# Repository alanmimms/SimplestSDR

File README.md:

# SimplestSDR
Very simple SDR to build on a breadboard to demonstrate SDR principles driving a PC sound input for I/Q.

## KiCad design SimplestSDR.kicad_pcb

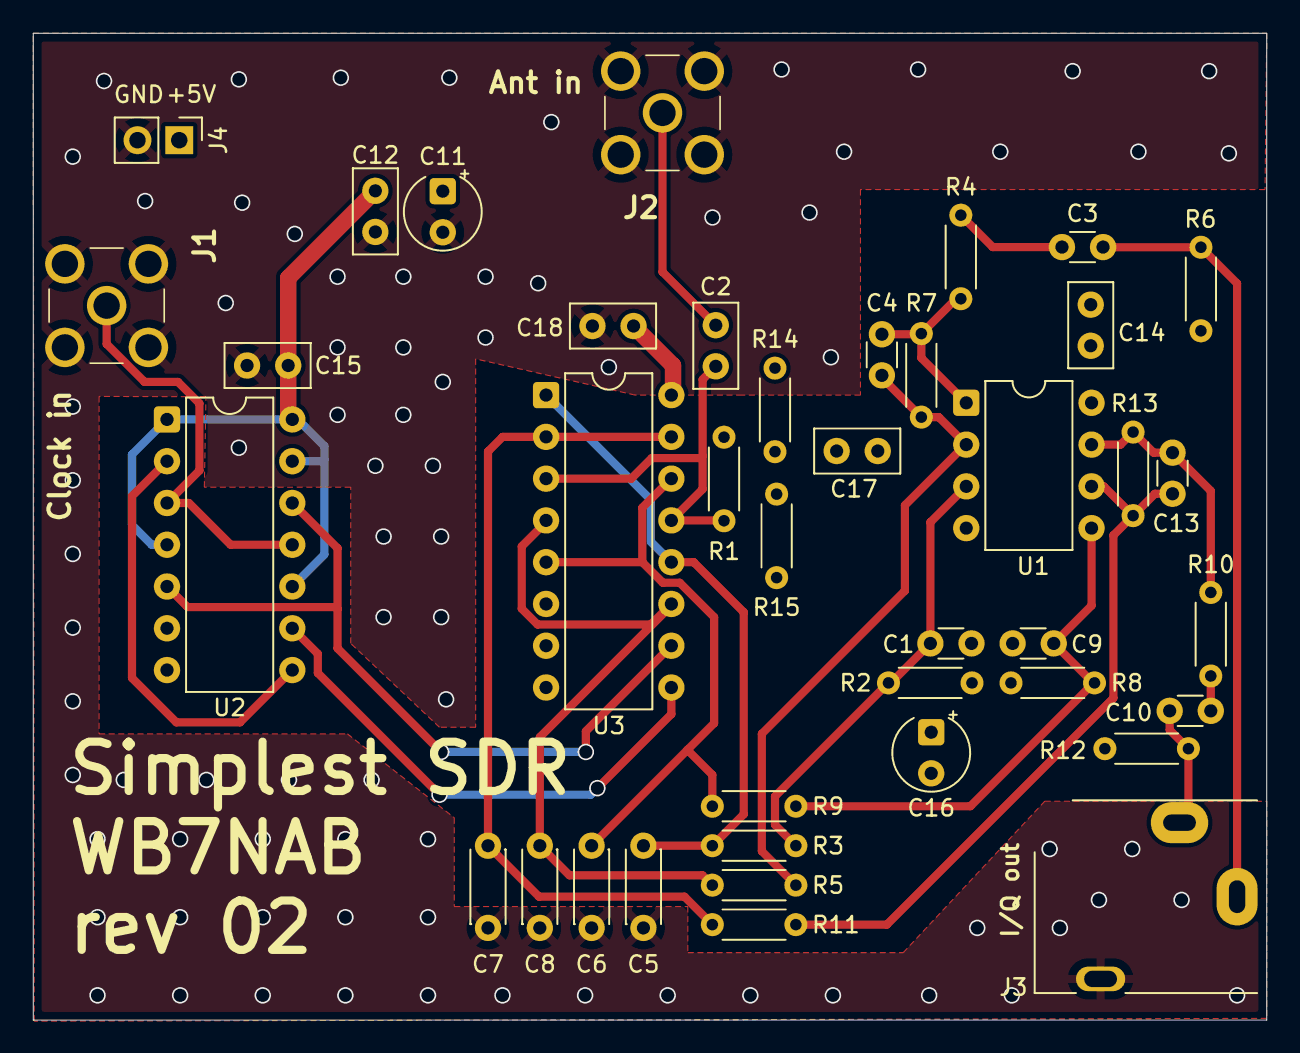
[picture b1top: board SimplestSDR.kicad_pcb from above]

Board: 2 copper layers, 75.0 x 60.0 mm, 40 parts (0 on the bottom side), 23 nets.

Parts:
C1, C4, C9, C13: 100pF; C_Disc_D3.0mm_W1.6mm_P2.50mm
C2, C12, C14, C15, C17, C18: 100nF; C_Disc_D5.0mm_W2.5mm_P2.50mm
C3, C10: 1uF; C_Disc_D3.0mm_W1.6mm_P2.50mm
C5, C6, C7, C8: 4.7nF; C_Disc_D4.3mm_W1.9mm_P5.00mm
C11, C16: 10uF; CP_Radial_Tantal_D4.5mm_P2.50mm
J1: Clock in; SMAJPHRATH1
J2: Ant in; SMAJPHRATH1
J3: I/Q out; Jack_3.5mm_CUI_SJ1-3513N_Horizontal
J4: +5V; PinHeader_1x02_P2.54mm_Vertical
R1: 1k; R_Axial_DIN0204_L3.6mm_D1.6mm_P5.08mm_Horizontal
R2, R6, R7, R8, R12, R13: 100k; R_Axial_DIN0204_L3.6mm_D1.6mm_P5.08mm_Horizontal
R3, R5, R9, R11, R14, R15: 10k; R_Axial_DIN0204_L3.6mm_D1.6mm_P5.08mm_Horizontal
R4, R10: 47; R_Axial_DIN0204_L3.6mm_D1.6mm_P5.08mm_Horizontal
U1: LM358AN; DIP-8_W7.62mm
U2: 74HC74; DIP-14_W7.62mm
U3: CD74HC4052E; DIP-16_W7.62mm

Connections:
GND: C5.2, C6.2, C7.2, C8.2, C11.2, C12.2, C14.2, C15.2, C16.2, C17.2, C18.2, J1.2 (GND), J1.3 (GND), J1.4 (GND), J1.5 (GND), J2.2 (GND), J2.3 (GND), J2.4 (GND), J2.5 (GND), J3.G, J4.2, R6.1, R12.1, R15.2, U1.4 (GND), U2.7 (GND), U3.6 (E_N), U3.7 (VEE), U3.8 (GND)
unnamed: C3.1, R4.2
unnamed: C3.2, J3.S, R6.2
unnamed: C10.1, R10.2
unnamed: C10.2, J3.T, R12.2
unnamed: J1.1 (In), U2.3 (C), U2.11 (C)
unnamed: C2.1, J2.1 (In)
unnamed: C1.1, R2.1, R3.2, U1.3 (IN+)
unnamed: C4.1, R5.2, R7.1, U1.2 (IN-)
unnamed: C4.2, R4.1, R7.2, U1.1 (OUT)
unnamed: C9.1, R8.1, R9.2, U1.5 (IN+)
unnamed: C13.1, R11.2, R13.1, U1.6 (IN-)
unnamed: C13.2, R10.1, R13.2, U1.7 (OUT)
unnamed: U2.2 (D), U2.8 (~Q)
unnamed: U2.5 (Q), U2.12 (D), U3.10 (S0)
unnamed: U2.9 (Q), U3.9 (S1)
unnamed: C5.1, R3.1, U3.1 (B0), U3.12 (A0)
unnamed: C6.1, R9.1, U3.5 (B1), U3.14 (A1)
unnamed: C7.1, R11.1, U3.2 (B2), U3.15 (A2)
unnamed: C8.1, R5.1, U3.4 (B3), U3.11 (A3)
unnamed: C2.2, R1.2, U3.3 (BN), U3.13 (AN)
VDD: C11.1, C12.1, C14.1, C15.1, C18.1, J4.1, R14.1, U1.8 (V+), U2.1 (~R), U2.4 (~S), U2.10 (~S), U2.13 (~R), U2.14 (VCC), U3.16 (VCC)
Vbias: C1.2, C9.2, C16.1, C17.1, R1.1, R2.2, R8.2, R14.2, R15.1
